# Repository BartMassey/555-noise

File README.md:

# 555 Noisemaker
Bart Massey 2013-02-04

This circuit is the "[Laser Ray
Sound](http://www.555-timer-circuits.com/laser-ray-sound.html)"
from <http://555-timer-circuits.com>,
layed out in [KiCAD](http://kicad-pcb.org) and
available under the "MIT License" (see the file COPYING in
this distribution for license terms).

There is a BOM file and Gerber artwork checked in, for those
who want to skip the KiCAD step. The parts are all from
Digikey, and have Digikey part numbers; unfortunately I
haven't yet figured out how to get KiCAD to take those
numbers.

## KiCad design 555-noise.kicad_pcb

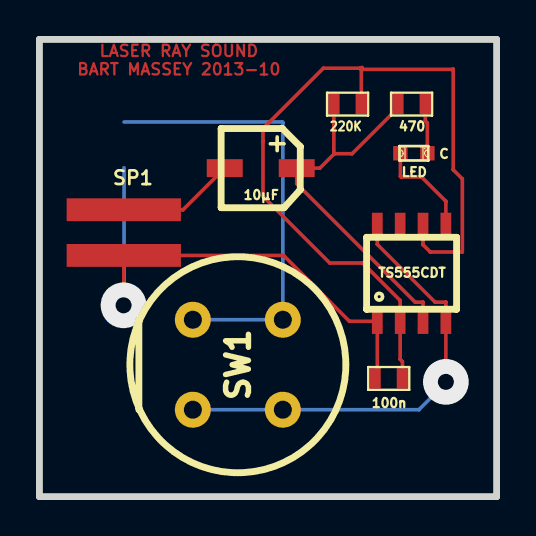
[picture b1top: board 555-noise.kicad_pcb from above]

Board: 2 copper layers, 25.4 x 25.4 mm, 9 parts (1 on the bottom side), 8 nets.

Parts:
BT1: BATTERY; WIRE_PADS_2x1
C1: 100n; SM0603
C2: 10μF; C_ELECTRO_AVE_B
D1: LED; CHIP_LED
R1: 470; SM0603
R2: 220K; SM0603
SP1: 8Ω SPKR; WIRE_PADS_2x1
SW1: SPST; ESWITCH
U1: TS555CDT; SO8E

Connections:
+9V: SW1.1, U1.4, U1.8
GND: BT1.2, C1.2, SP1.2, U1.1
unnamed: D1.1, U1.5
unnamed: BT1.1, SW1.2
unnamed: C2.2, SP1.1
unnamed: C2.1, R1.1, R2.2, U1.3
unnamed: C1.1, R2.1, U1.2, U1.6
unnamed: D1.2, R1.2

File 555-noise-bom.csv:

ref,value
BT1,BATTERY
C1,100n
C2,10u
D1,LED
R1,470
R2,220K
SP1,8ohm SPEAKER
SW1,SPST
U1,TS555CDT

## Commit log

2013-02-01 Laser Ray Sound board in KiCAD
2013-02-01 incorporated changes from work computer
2013-02-04 included changes (including regressions) from laptop
2013-02-04 added README, COPYING
2013-02-04 reached likely ready-to-go artwork
2013-02-08 converted via to rivet-style
2013-02-12 removed front-side wart; shrank solder 20%; shrank text thickness
2013-02-12 dramatically increased via pad for extra rivet squashage; cleaned up silk a bit
2013-10-06 updated board for second router turn
2013-10-06 finished rev 2 board for pcb router
2013-10-07 added front paste in SVG and PDF
2013-10-08 updated and packaged for OSH Park; not yet ready to submit
2013-10-08 version finally shipped to OSHPark
2013-10-08 merged fixes from OSHPark version
